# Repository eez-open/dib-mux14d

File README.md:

### Ownership and License
The contributors are listed in CONTRIB.TXT.

Licenses | OSHWA UID
--|--
 | 

### Overview

The EEZ DIB MUX14D module features two 7:1 reed relay 2-wire multiplexer that can be connect together to make single 14:1 multiplexer. 

### Feature list

* On-board STM32F030C6T6 or STM32F031C4T6 MCU 
* 2 x 16-pin dual row 3.81 mm connectors
* 2 x ADIB connectors (10-pin 2 mm), ADIB ID=002
* Dual 2-wire 7:1 reed relay 2-line multiplexer 
* On-board +3.3 V LDO
* Firmware download via UART
* Optional SWD for debugging
* I2C EEPROM for storing board specific parameters
* Dimensions: 131 x 95 mm, 2-layer PCB

### r1B2 prototype

### Firmware repository

https://github.com/eez-open/dib-mux14d-fw  
The firmware download procedure is described in [Chapter 13.2]((https://www.envox.eu/eez-bench-box-3/bb3-user-manual/13-firmware-upgrade/#bb3_man_module_upgrade) of the User Manual.

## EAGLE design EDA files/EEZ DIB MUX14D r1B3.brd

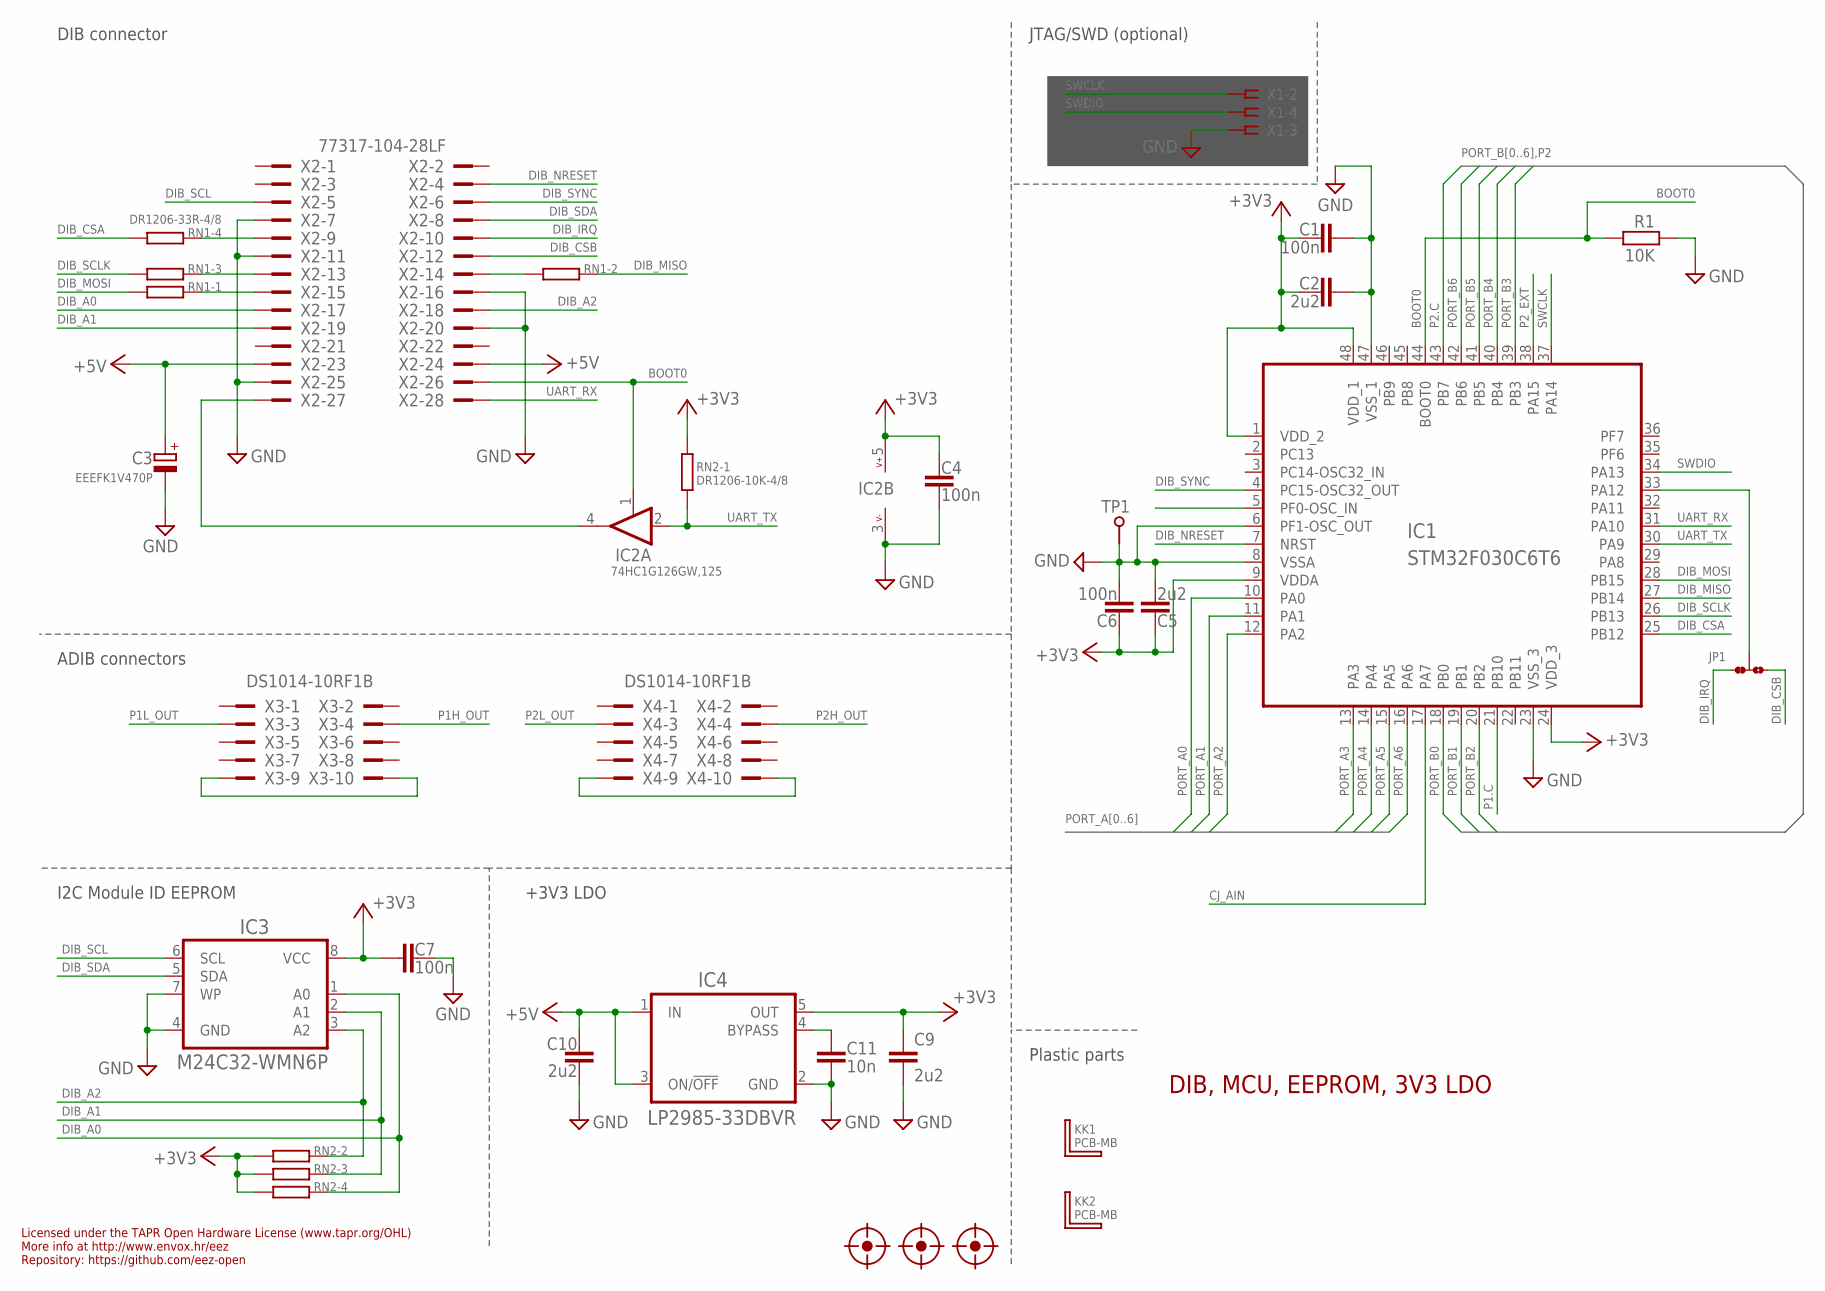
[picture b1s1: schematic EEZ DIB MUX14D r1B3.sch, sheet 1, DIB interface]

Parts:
C1, C4, C6, C7: 100n; C0603
C2, C5, C9, C10: 2u2; C0805
C3: EEEFK1V470P; CAPAE660X610N
C11: 10n; C0805
FM1, FM2, FM3: FIDUCIAL_2; FIDUCIAL_DUAL
IC1: STM32F030C6T6; LQFP-48
IC2: 74HC1G126GW,125; SOT65P210X110-5N
IC3: M24C32-WMN6P; SOIC127P600X173-8N
IC4: LP2985-33DBVR; SOT95P270X145-5N
JP1: JP3-CUT-0805-ROTATED; JP3-0805-CUT2
KK1, KK2: PCB-MB
R1: 10K; R0805
RN1: DR1206-33R-4/8; CAY16
RN2: DR1206-10K-4/8; CAY16
TP1: PCB_TEST_TABSHIELD; PCB_SHIELD_TAB
X1: N.C.; SSW-106-02-S-S
X2: 77317-104-28LF
X3, X4: DS1014-10RF1B

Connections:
+3V3: C1.2, C2.1, C4.1, C5.2, C6.1, C7.2, C9.1, IC1.1 (VDD_2), IC1.9 (VDDA), IC1.24 (VDD_3), IC1.48 (VDD_1), IC2.5 (V+), IC3.8 (VCC), IC4.5 (OUT), RN2.5 (2), RN2.6 (2), RN2.7 (2), RN2.8 (2); also elsewhere on the board
+5V: C3.1 (+), C10.2, IC4.1 (IN), IC4.3 (ON/!OFF), X2.23, X2.24; also elsewhere on the board
BOOT0: IC1.44 (BOOT0), IC2.1 (EN), R1.2, X2.26
CJ_AIN: IC1.17 (PA7); also elsewhere on the board
DIB_A0: IC3.1 (A0), RN2.4 (1), X2.17
DIB_A1: IC3.2 (A1), RN2.3 (1), X2.19
DIB_A2: IC3.3 (A2), RN2.2 (1), X2.18
DIB_CSA: IC1.25 (PB12), RN1.4 (1)
DIB_CSB: JP1.NO, X2.12
DIB_IRQ: JP1.NC, X2.10
DIB_MISO: IC1.27 (PB14), RN1.2 (1)
DIB_MOSI: IC1.28 (PB15), RN1.1
DIB_NRESET: IC1.7 (NRST), X2.4
DIB_SCL: IC3.6 (SCL), X2.5
DIB_SCLK: IC1.26 (PB13), RN1.3 (1)
DIB_SDA: IC3.5 (SDA), X2.8
DIB_SYNC: IC1.4 (PC15-OSC32_OUT), X2.6
GND: C1.1, C2.2, C3.2 (-), C4.2, C5.1, C6.2, C7.1, C9.2, C10.1, C11.1, IC1.6 (PF1-OSC_OUT), IC1.8 (VSSA), IC1.23 (VSS_3), IC1.47 (VSS_1), IC2.3 (V-), IC3.4 (GND), IC3.7 (WP), IC4.2 (GND), R1.1, TP1.1, X1.3, X2.7, X2.11, X2.16, X2.20, X2.25; also elsewhere on the board
unnamed: X3.9, X3.10
unnamed: X4.9, X4.10
unnamed: RN1.5 (2), X2.9
unnamed: C11.2, IC4.4 (BYPASS)
unnamed: IC2.4 (O), X2.27
unnamed: IC1.33 (PA12), JP1.COM
unnamed: RN1.6 (2), X2.13
unnamed: RN1.7 (2), X2.14
unnamed: RN1.8 (2), X2.15
P1.C: IC1.21 (PB10); also elsewhere on the board
P1H_OUT: X3.4; also elsewhere on the board
P1L_OUT: X3.3; also elsewhere on the board
P2.C: IC1.43 (PB7); also elsewhere on the board
P2H_OUT: X4.4; also elsewhere on the board
P2L_OUT: X4.3; also elsewhere on the board
P2_EXT: IC1.38 (PA15); also elsewhere on the board
PORT_A0: IC1.10 (PA0); also elsewhere on the board
PORT_A1: IC1.11 (PA1); also elsewhere on the board
PORT_A2: IC1.12 (PA2); also elsewhere on the board
PORT_A3: IC1.13 (PA3); also elsewhere on the board
PORT_A4: IC1.14 (PA4); also elsewhere on the board
PORT_A5: IC1.15 (PA5); also elsewhere on the board
PORT_A6: IC1.16 (PA6); also elsewhere on the board
PORT_B0: IC1.18 (PB0); also elsewhere on the board
PORT_B1: IC1.19 (PB1); also elsewhere on the board
PORT_B2: IC1.20 (PB2); also elsewhere on the board
PORT_B3: IC1.39 (PB3); also elsewhere on the board
PORT_B4: IC1.40 (PB4); also elsewhere on the board
PORT_B5: IC1.41 (PB5); also elsewhere on the board
PORT_B6: IC1.42 (PB6); also elsewhere on the board
SWCLK: IC1.37 (PA14), X1.2
SWDIO: IC1.34 (PA13), X1.4
UART_RX: IC1.31 (PA10), X2.28
UART_TX: IC1.30 (PA9), IC2.2 (I), RN2.1

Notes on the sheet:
Licensed under the TAPR Open Hardware License (www.tapr.org/OHL)
Repository: https://github.com/eez-open
More info at http://www.envox.hr/eez
DIB, MCU, EEPROM, 3V3 LDO
Plastic parts
I2C Module ID EEPROM
+3V3 LDO
JTAG/SWD (optional)
DIB connector
ADIB connectors

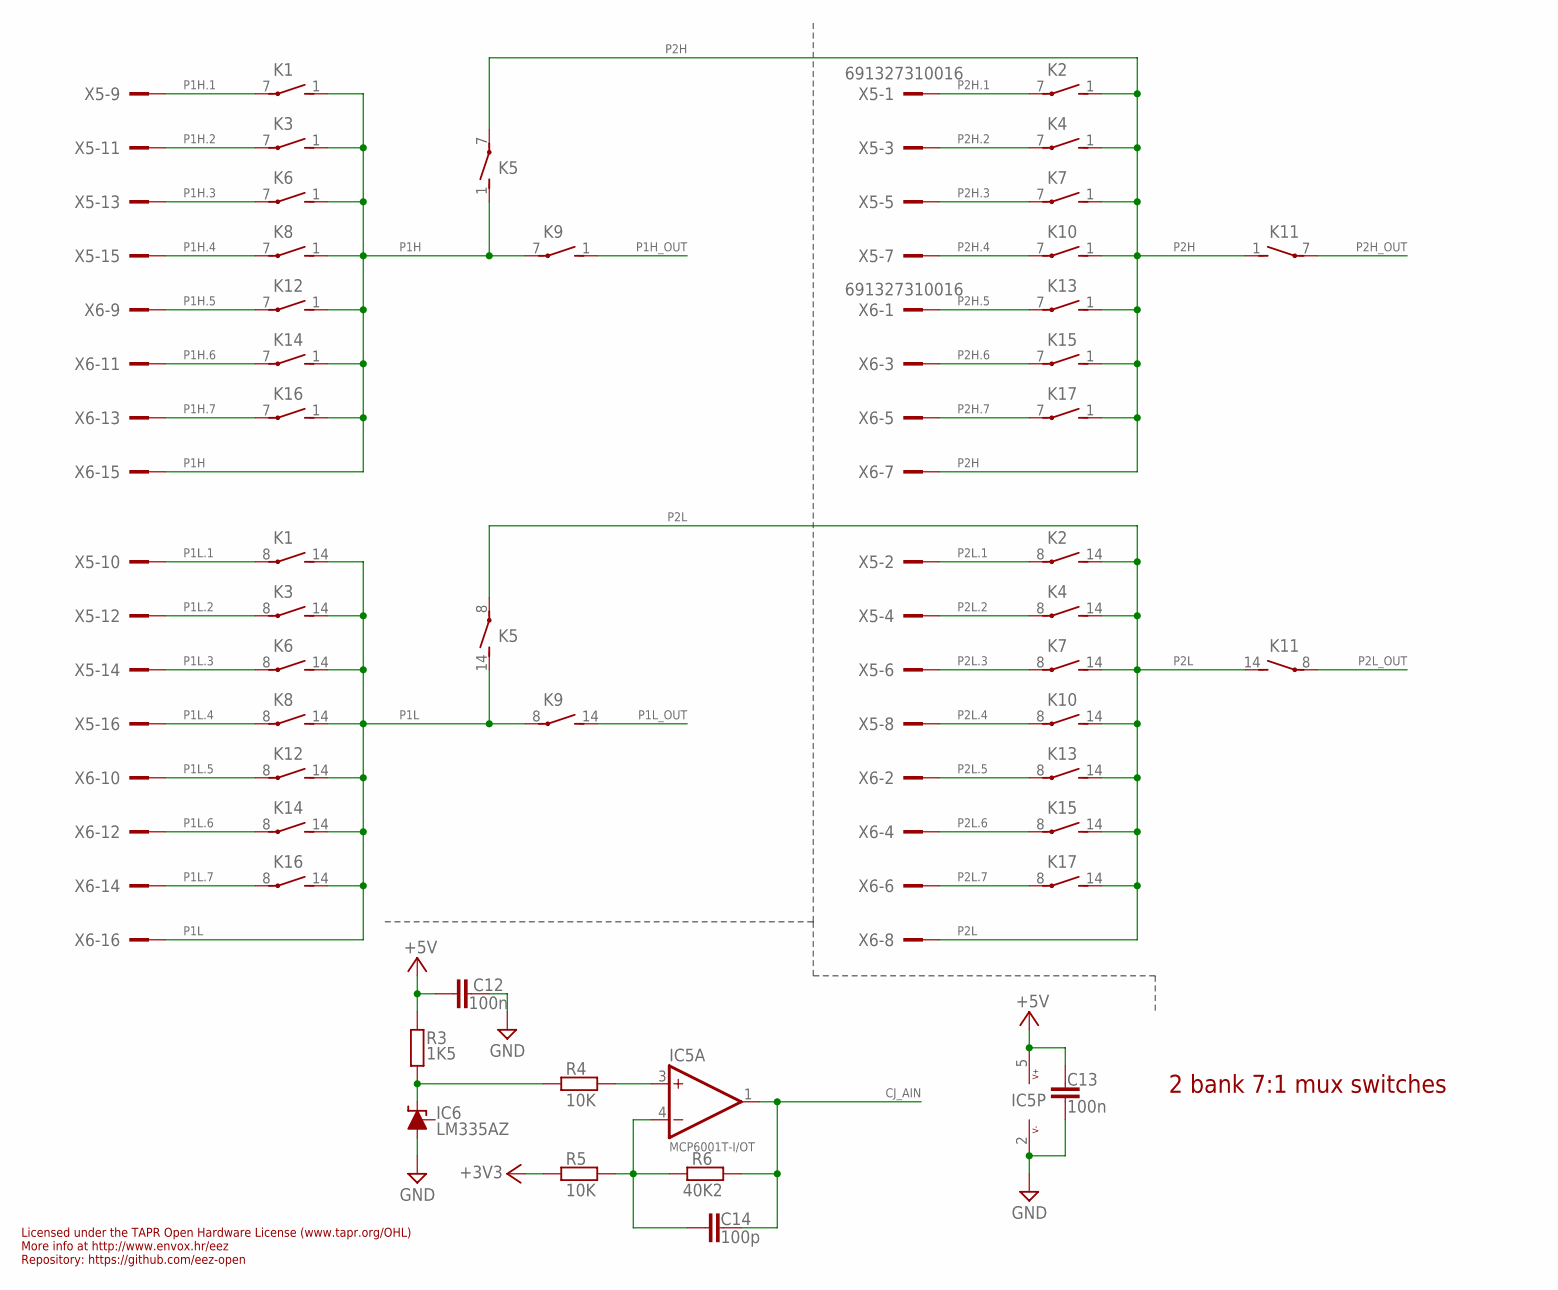
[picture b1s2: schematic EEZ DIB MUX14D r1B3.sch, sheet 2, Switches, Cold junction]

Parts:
C12, C13: 100n; C0603
C14: 100p; C0805
IC5: MCP6001T-I/OT; DBV5
IC6: LM335AZ; TO92
K1, K2, K3, K4, K6, K7, K8, K9, K10, K11, K12, K13, K14, K15, K16, K17: HE722A0500; RR2A
K5: HE721A0500; RR2A
R3: 1K5; R0805
R4, R5: 10K; R0805
R6: 40K2; R0805
X5, X6: 691327310016

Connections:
+3V3: R5.2; also elsewhere on the board
+5V: C12.1, C13.1, IC5.5 (V+), R3.1; also elsewhere on the board
CJ_AIN: C14.2, IC5.1 (OUT), R6.1; also elsewhere on the board
GND: C12.2, C13.2, IC5.2 (V-), IC6.3 (A); also elsewhere on the board
unnamed: IC6.2 (C), R3.2, R4.2
unnamed: C14.1, IC5.4 (-IN), R5.1, R6.2
unnamed: IC5.3 (+IN), R4.1
P1H: K1.1 (S), K3.1 (S), K5.1 (S), K6.1 (S), K8.1 (S), K9.7, K12.1 (S), K14.1 (S), K16.1 (S), X6.15
P1H.1: K1.7, X5.9
P1H.2: K3.7, X5.11
P1H.3: K6.7, X5.13
P1H.4: K8.7, X5.15
P1H.5: K12.7, X6.9
P1H.6: K14.7, X6.11
P1H.7: K16.7, X6.13
P1H_OUT: K9.1 (S); also elsewhere on the board
P1L: K1.14 (S), K3.14 (S), K5.14 (S), K6.14 (S), K8.14 (S), K9.8, K12.14 (S), K14.14 (S), K16.14 (S), X6.16
P1L.1: K1.8, X5.10
P1L.2: K3.8, X5.12
P1L.3: K6.8, X5.14
P1L.4: K8.8, X5.16
P1L.5: K12.8, X6.10
P1L.6: K14.8, X6.12
P1L.7: K16.8, X6.14
P1L_OUT: K9.14 (S); also elsewhere on the board
P2H: K2.1 (S), K4.1 (S), K5.7, K7.1 (S), K10.1 (S), K11.1 (S), K13.1 (S), K15.1 (S), K17.1 (S), X6.7
P2H.1: K2.7, X5.1
P2H.2: K4.7, X5.3
P2H.3: K7.7, X5.5
P2H.4: K10.7, X5.7
P2H.5: K13.7, X6.1
P2H.6: K15.7, X6.3
P2H.7: K17.7, X6.5
P2H_OUT: K11.7; also elsewhere on the board
P2L: K2.14 (S), K4.14 (S), K5.8, K7.14 (S), K10.14 (S), K11.14 (S), K13.14 (S), K15.14 (S), K17.14 (S), X6.8
P2L.1: K2.8, X5.2
P2L.2: K4.8, X5.4
P2L.3: K7.8, X5.6
P2L.4: K10.8, X5.8
P2L.5: K13.8, X6.2
P2L.6: K15.8, X6.4
P2L.7: K17.8, X6.6
P2L_OUT: K11.8; also elsewhere on the board

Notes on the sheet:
Licensed under the TAPR Open Hardware License (www.tapr.org/OHL)
Repository: https://github.com/eez-open
More info at http://www.envox.hr/eez
2 bank 7:1 mux switches

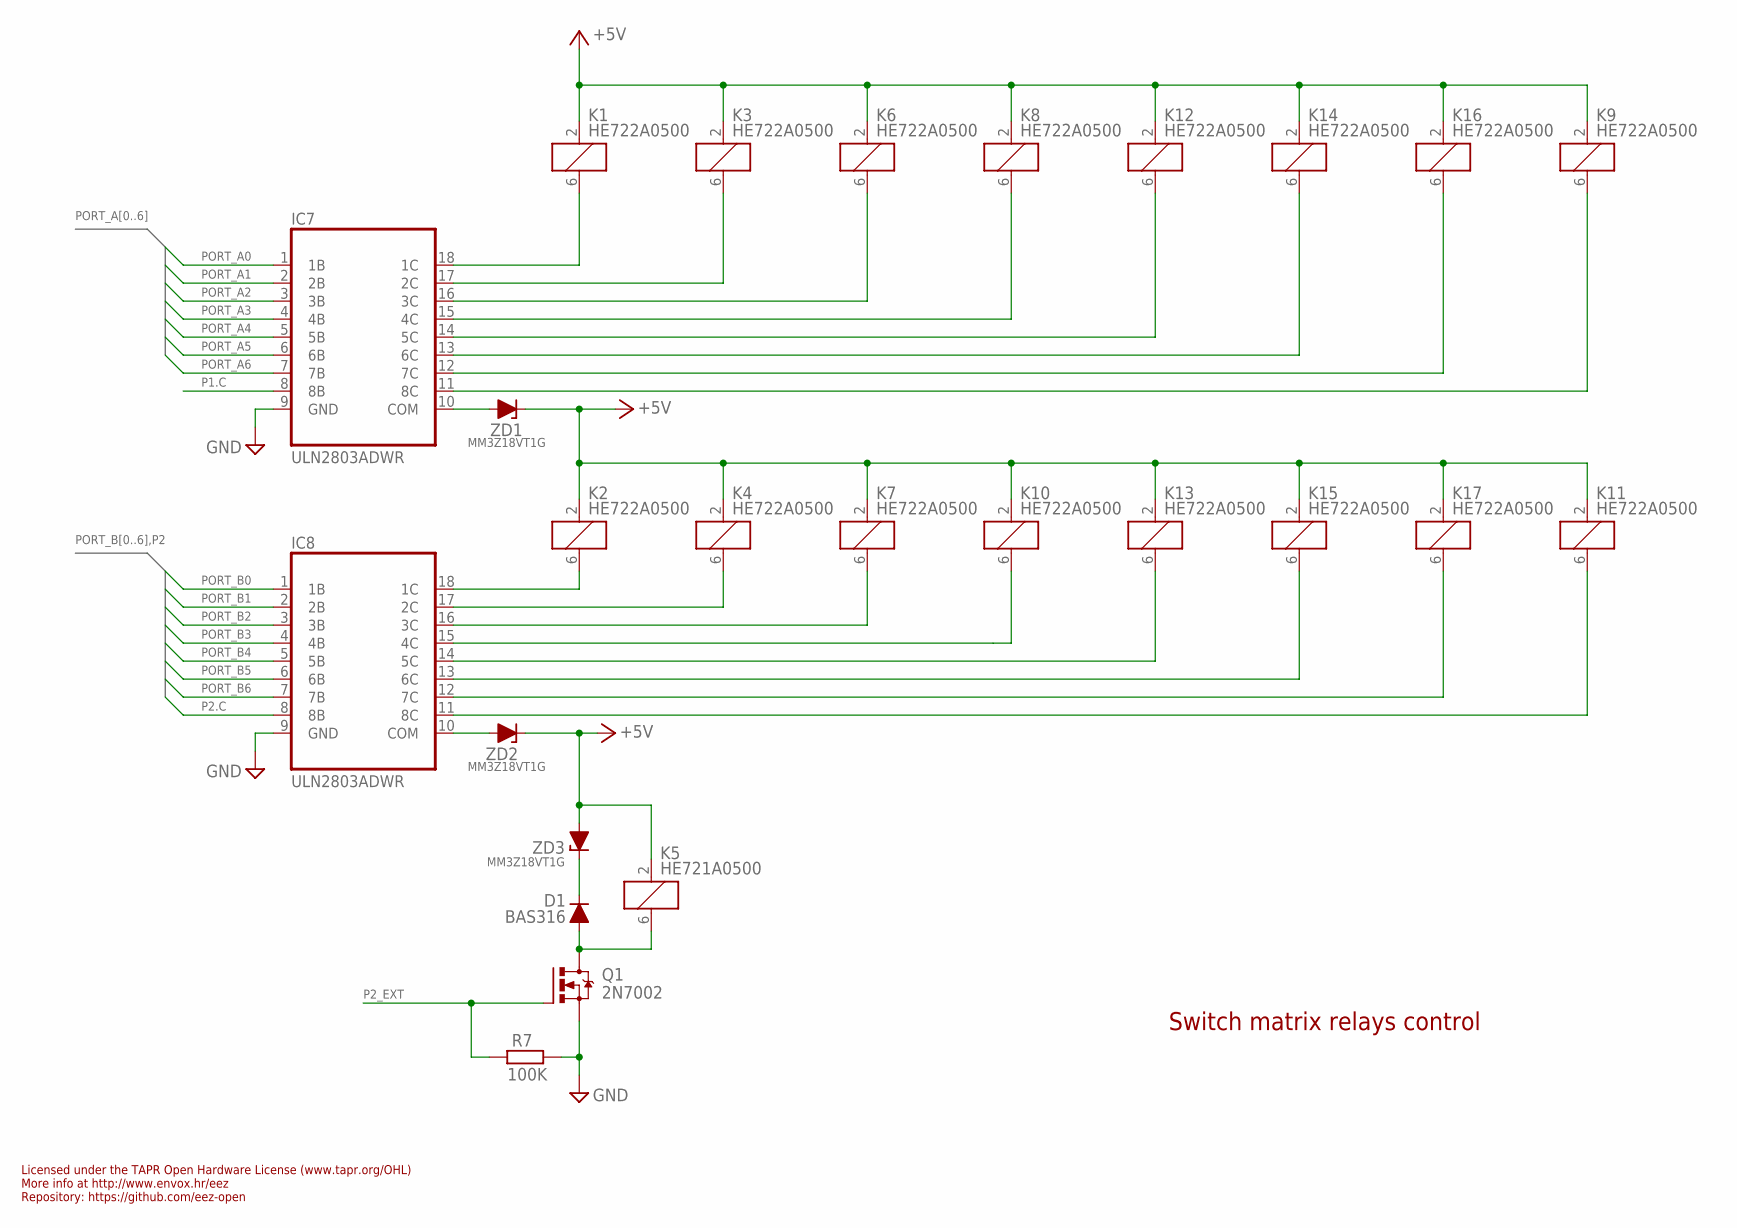
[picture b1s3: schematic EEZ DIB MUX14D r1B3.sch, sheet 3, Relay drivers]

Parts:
D1: BAS316; SOD323-R
IC7, IC8: ULN2803ADWR; DW18_TEX-M
K1, K2, K3, K4, K6, K7, K8, K9, K10, K11, K12, K13, K14, K15, K16, K17: HE722A0500; RR2A
K5: HE721A0500; RR2A
Q1: 2N7002; SOT103P240X110-3N; MPN 2N7002-7-F
R7: 100K; R0805
ZD1, ZD2, ZD3: MM3Z18VT1G; SOD323-R

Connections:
+5V: K1.2 (1), K2.2 (1), K3.2 (1), K4.2 (1), K5.2 (1), K6.2 (1), K7.2 (1), K8.2 (1), K9.2 (1), K10.2 (1), K11.2 (1), K12.2 (1), K13.2 (1), K14.2 (1), K15.2 (1), K16.2 (1), K17.2 (1), ZD1.C, ZD2.C, ZD3.A; also elsewhere on the board
GND: IC7.9 (GND), IC8.9 (GND), Q1.2 (S), R7.2; also elsewhere on the board
unnamed: D1.C, ZD3.C
unnamed: IC7.10 (COM), ZD1.A
unnamed: IC7.18 (1C), K1.6 (2)
unnamed: IC7.17 (2C), K3.6 (2)
unnamed: IC7.16 (3C), K6.6 (2)
unnamed: IC7.15 (4C), K8.6 (2)
unnamed: IC7.14 (5C), K12.6 (2)
unnamed: IC7.13 (6C), K14.6 (2)
unnamed: IC7.12 (7C), K16.6 (2)
unnamed: IC7.11 (8C), K9.6 (2)
unnamed: D1.A, K5.6 (2), Q1.3 (D)
unnamed: IC8.10 (COM), ZD2.A
unnamed: IC8.18 (1C), K2.6 (2)
unnamed: IC8.17 (2C), K4.6 (2)
unnamed: IC8.16 (3C), K7.6 (2)
unnamed: IC8.15 (4C), K10.6 (2)
unnamed: IC8.14 (5C), K13.6 (2)
unnamed: IC8.13 (6C), K15.6 (2)
unnamed: IC8.12 (7C), K17.6 (2)
unnamed: IC8.11 (8C), K11.6 (2)
P1.C: IC7.8 (8B); also elsewhere on the board
P2.C: IC8.8 (8B); also elsewhere on the board
P2_EXT: Q1.1 (G), R7.1; also elsewhere on the board
PORT_A0: IC7.1 (1B); also elsewhere on the board
PORT_A1: IC7.2 (2B); also elsewhere on the board
PORT_A2: IC7.3 (3B); also elsewhere on the board
PORT_A3: IC7.4 (4B); also elsewhere on the board
PORT_A4: IC7.5 (5B); also elsewhere on the board
PORT_A5: IC7.6 (6B); also elsewhere on the board
PORT_A6: IC7.7 (7B); also elsewhere on the board
PORT_B0: IC8.1 (1B); also elsewhere on the board
PORT_B1: IC8.2 (2B); also elsewhere on the board
PORT_B2: IC8.3 (3B); also elsewhere on the board
PORT_B3: IC8.4 (4B); also elsewhere on the board
PORT_B4: IC8.5 (5B); also elsewhere on the board
PORT_B5: IC8.6 (6B); also elsewhere on the board
PORT_B6: IC8.7 (7B); also elsewhere on the board

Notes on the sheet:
Licensed under the TAPR Open Hardware License (www.tapr.org/OHL)
Repository: https://github.com/eez-open
More info at http://www.envox.hr/eez
Switch matrix relays control

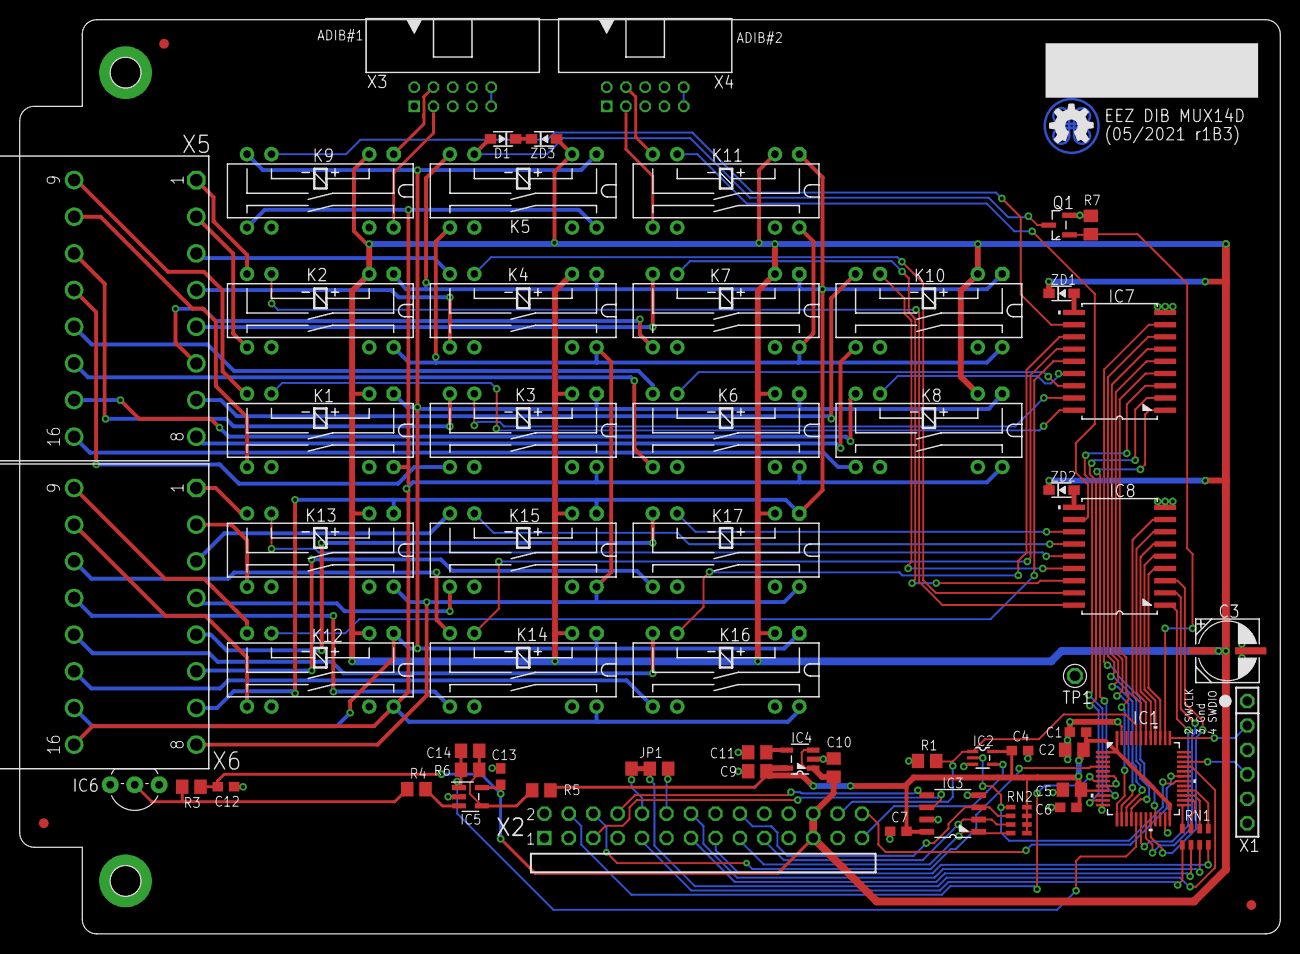
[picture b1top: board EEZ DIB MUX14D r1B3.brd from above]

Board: 2 copper layers, 131.0 x 95.0 mm, 65 parts (0 on the bottom side), 107 nets.

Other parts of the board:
EEZ_SIGNATURE: SIGNATURESMALL; SIGNATURE_5MM

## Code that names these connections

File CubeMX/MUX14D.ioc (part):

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Mcu.Name=STM32F030C6Tx
Mcu.Package=LQFP48
Mcu.UserName=STM32F030C6Tx
PA0.GPIOParameters=GPIO_Label
PA0.GPIO_Label=P1.0
PA0.Signal=GPIO_Output
PA1.GPIOParameters=GPIO_Label
PA1.GPIO_Label=P1.1
PA1.Signal=GPIO_Output
PA10.Mode=Asynchronous
PA10.Signal=USART1_RX
PA12.GPIOParameters=GPIO_Label
PA12.GPIO_Label=DIB_IRQ
PA12.Signal=GPIO_Output
PA13.Mode=Serial_Wire
PA13.Signal=SYS_SWDIO
PA14.Mode=Serial_Wire
PA14.Signal=SYS_SWCLK
PA15.GPIOParameters=GPIO_Label
PA15.GPIO_Label=P2_EXT
PA15.Signal=GPIO_Output
PA2.GPIOParameters=GPIO_Label
PA2.GPIO_Label=P1.2
PA2.Signal=GPIO_Output
PA3.GPIOParameters=GPIO_Label
PA3.GPIO_Label=P1.3
PA3.Signal=GPIO_Output
PA4.GPIOParameters=GPIO_Label
PA4.GPIO_Label=P1.4
PA4.Signal=GPIO_Output
PA5.GPIOParameters=GPIO_Label
PA5.GPIO_Label=P1.5
PA5.Signal=GPIO_Output
PA6.GPIOParameters=GPIO_Label
PA6.GPIO_Label=P1.6
PA6.Signal=GPIO_Output
PA7.GPIOParameters=GPIO_Label
PA7.GPIO_Label=P1.7
PA7.Signal=GPIO_Output
PA9.Mode=Asynchronous
PA9.Signal=USART1_TX
PB0.GPIOParameters=GPIO_Label
PB0.GPIO_Label=P2.0
PB0.Signal=GPIO_Output
PB1.GPIOParameters=GPIO_Label
PB1.GPIO_Label=P2.1
PB1.Signal=GPIO_Output
PB12.GPIOParameters=GPIO_Label
PB12.GPIO_Label=DIB_CSA
PB12.Mode=NSS_Signal_Hard_Input
PB12.Signal=SPI1_NSS
PB13.GPIOParameters=GPIO_Label
PB13.GPIO_Label=DIB_SCLK
PB13.Mode=Full_Duplex_Slave
PB13.Signal=SPI1_SCK
PB14.GPIOParameters=GPIO_Label
PB14.GPIO_Label=DIB_MISO
PB14.Mode=Full_Duplex_Slave
PB14.Signal=SPI1_MISO
PB15.GPIOParameters=GPIO_Label
PB15.GPIO_Label=DIB_MOSI
PB15.Mode=Full_Duplex_Slave
PB15.Signal=SPI1_MOSI
PB2.GPIOParameters=GPIO_Label
PB2.GPIO_Label=P2.2
PB2.Signal=GPIO_Output
PB3.GPIOParameters=GPIO_Label
PB3.GPIO_Label=P2.3
PB3.Signal=GPIO_Output
PB4.GPIOParameters=GPIO_Label
PB4.GPIO_Label=P2.4
PB4.Signal=GPIO_Output
PB5.GPIOParameters=GPIO_Label
PB5.GPIO_Label=P2.5
PB5.Signal=GPIO_Output
PB6.GPIOParameters=GPIO_Label
PB6.GPIO_Label=P2.6
PB6.Signal=GPIO_Output
PB7.GPIOParameters=GPIO_Label
PB7.GPIO_Label=P2.7
PB7.Signal=GPIO_Output
PC15-OSC32_OUT.GPIOParameters=GPIO_Label
PC15-OSC32_OUT.GPIO_Label=DIB_SYNC
PC15-OSC32_OUT.Signal=GPIO_Input
board=custom

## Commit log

2020-12-08 K9, K8, K17 rotated on PCB
2020-12-19 ADIB ID=002
2021-01-22 small PCB layout corrections
2021-01-30 PCB ID added
2021-01-31 BOM update
2021-03-28 Centroid files
2021-03-28 Module front mask
2021-04-10 prototype image updated
2021-10-08 OSHWA UID
2022-06-14 Reed relay replacement
2022-07-01 Reed relay model correction

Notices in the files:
parts and their libraries:
EEZ_DIB: This work is licensed under the TAPR Open Hardware License.
